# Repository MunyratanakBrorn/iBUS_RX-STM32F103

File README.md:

# iBUS_RX-STM32F103
iBUS RX using nRF24l01+ with STM32F103

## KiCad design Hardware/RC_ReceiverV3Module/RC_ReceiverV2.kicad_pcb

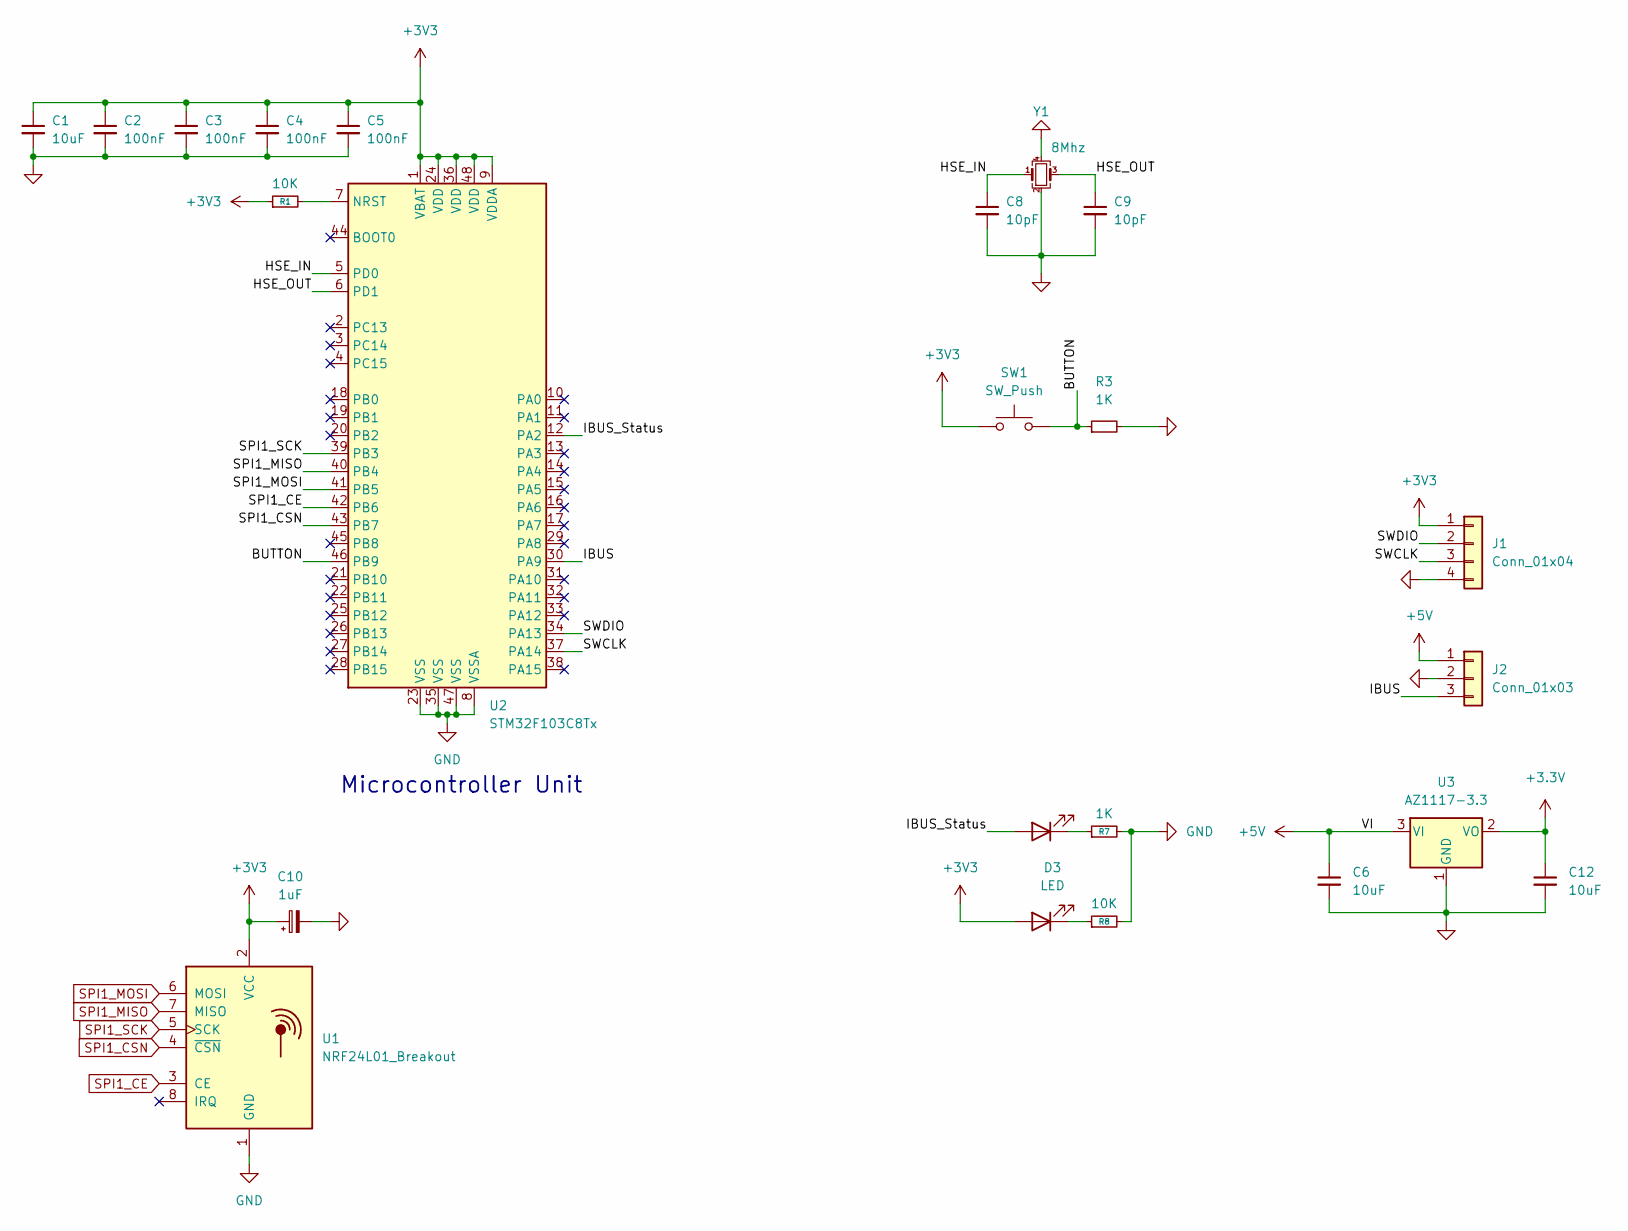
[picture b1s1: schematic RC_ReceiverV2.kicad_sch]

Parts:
C1, C6, C12: 10uF; C_0603_1608Metric
C2, C3, C4, C5: 100nF; C_0603_1608Metric
C8, C9: 10pF; C_0603_1608Metric
C10: 1uF; CP_EIA-3216-10_Kemet-I
D2, D3: LED; LED_0603_1608Metric
J1: Conn_01x04; ConPadx04
J2: Conn_01x03; Molex_Pico-Clasp_202396-0307_1x03-1MP_P1.00mm_Horizontal
R1, R8: 10K; R_0603_1608Metric
R3, R7: 1K; R_0603_1608Metric
SW1: SW_Push; SW_SPST_PTS810
U1: NRF24L01_Breakout; AS01-SPI
U2: STM32F103C8Tx; LQFP-48_7x7mm_P0.5mm
U3: AZ1117-3.3; SOT-89-3
Y1: 8Mhz; Crystal_SMD_3225-4Pin_3.2x2.5mm

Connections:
+5V: C6.1, J2.1, U3.3 (VI)
/BUTTON: R3.1, SW1.2, U2.46 (PB9)
/HSE_IN: C8.1, U2.5 (PD0), Y1.1
/HSE_OUT: C9.1, U2.6 (PD1), Y1.3
/IBUS: J2.3, U2.30 (PA9)
/IBUS_Status: D2.2 (A), U2.12 (PA2)
/SWCLK: J1.3, U2.37 (PA14)
/SWDIO: J1.2, U2.34 (PA13)
GND: C1.2, C2.2, C3.2, C4.2, C5.2, C6.2, C8.2, C9.2, C10.2, C12.2, J1.4, J2.2, R3.2, R7.2, R8.2, U1.1 (GND), U2.8 (VSSA), U2.23 (VSS), U2.35 (VSS), U2.47 (VSS), U3.1 (GND), Y1.2, Y1.4
unnamed: D2.1 (K), R7.1
unnamed: D3.1 (K), R8.1
unnamed: R1.2, U2.7 (NRST)
SPI1_CE: U1.3 (CE), U2.42 (PB6)
SPI1_CSN: U1.4 (~CSN), U2.43 (PB7)
SPI1_MISO: U1.7 (MISO), U2.40 (PB4)
SPI1_MOSI: U1.6 (MOSI), U2.41 (PB5)
SPI1_SCK: U1.5 (SCK), U2.39 (PB3)

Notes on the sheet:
Microcontroller Unit

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
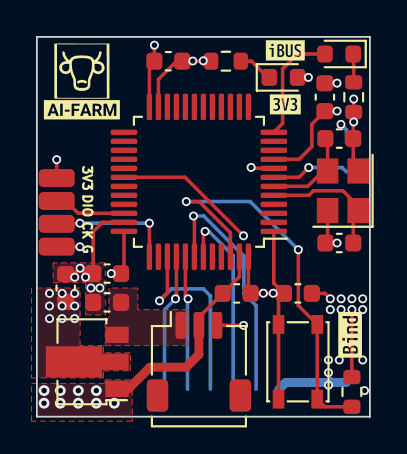
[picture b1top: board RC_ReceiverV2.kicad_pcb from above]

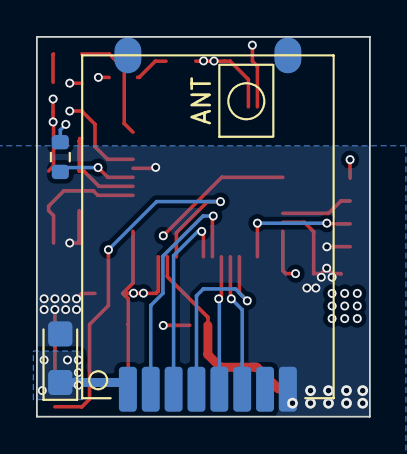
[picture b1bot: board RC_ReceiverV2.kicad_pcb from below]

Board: 4 copper layers, 18.5 x 21.1 mm, 27 parts (3 on the bottom side), 18 nets.

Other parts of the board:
kibuzzard-64FE91C5: G***; kibuzzard-64FE91C5
kibuzzard-64FE913F: G***; kibuzzard-64FE913F
kibuzzard-64FE9168: G***; kibuzzard-64FE9168
kibuzzard-6476ECD1: G***; kibuzzard-6476ECD1

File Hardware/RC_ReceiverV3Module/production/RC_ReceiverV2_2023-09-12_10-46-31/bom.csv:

Designator,Footprint,Quantity,Value,LCSC Part #
"C1, C12, C6",0603,3,10uF,
C10,CP_EIA-3216-10_Kemet-I,1,1uF,
"C2, C3, C4, C5",0603,4,100nF,
"C8, C9",0603,2,10pF,
"D2, D3",0603,2,LED,
J1,ConPadx04,1,Conn_01x04,
J2,Molex_Pico-Clasp_202396-0307_1x03-1MP_P1.00mm_Horizontal,1,Conn_01x03,
"R1, R8",0603,2,10K,
"R3, R7",0603,2,1K,
SW1,SW_SPST_PTS810,1,SW_Push,
U1,AS01-SPI,1,NRF24L01_Breakout,
U2,LQFP-48_7x7mm_P0.5mm,1,STM32F103C8Tx,
U3,SOT-89-3,1,AZ1117-3.3,
Y1,Crystal_SMD_3225-4Pin_3.2x2.5mm,1,8Mhz,

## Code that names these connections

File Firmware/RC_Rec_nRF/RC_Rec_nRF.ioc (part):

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Mcu.Name=STM32F103C(8-B)Tx
Mcu.Package=LQFP48
Mcu.UserName=STM32F103C8Tx
PA10.Mode=Asynchronous
PA10.Signal=USART1_RX
PA13.Mode=Serial_Wire
PA13.Signal=SYS_JTMS-SWDIO
PA14.Mode=Serial_Wire
PA14.Signal=SYS_JTCK-SWCLK
PA2.GPIOParameters=GPIO_Label
PA2.GPIO_Label=LED1
PA2.Signal=GPIO_Output
PA9.Mode=Asynchronous
PA9.Signal=USART1_TX
PB10.GPIOParameters=GPIO_Label
PB10.GPIO_Label=BUTTON1
PB10.Signal=GPIO_Input
PB3.Mode=Full_Duplex_Master
PB3.Signal=SPI1_SCK
PB4.Mode=Full_Duplex_Master
PB4.Signal=SPI1_MISO
PB5.Mode=Full_Duplex_Master
PB5.Signal=SPI1_MOSI
PB6.GPIOParameters=GPIO_Label
PB6.GPIO_Label=SPI1_CE
PB6.Signal=GPIO_Output
PB7.GPIOParameters=GPIO_Label
PB7.GPIO_Label=SPI1_CSN
PB7.Signal=GPIO_Output
PB9.GPIOParameters=GPIO_Label
PB9.GPIO_Label=BUTTON
PB9.Signal=GPIO_Input
PC13-TAMPER-RTC.Signal=GPIO_Output
PC14-OSC32_IN.GPIOParameters=GPIO_Label
PC14-OSC32_IN.GPIO_Label=SBUS_ST
PC14-OSC32_IN.Signal=GPIO_Output
PD0-OSC_IN.Mode=HSE-External-Oscillator
PD0-OSC_IN.Signal=RCC_OSC_IN
PD1-OSC_OUT.Mode=HSE-External-Oscillator
PD1-OSC_OUT.Signal=RCC_OSC_OUT
RCC.SYSCLKFreq_VALUE=72000000
RCC.SYSCLKSource=RCC_SYSCLKSOURCE_PLLCLK
board=custom
